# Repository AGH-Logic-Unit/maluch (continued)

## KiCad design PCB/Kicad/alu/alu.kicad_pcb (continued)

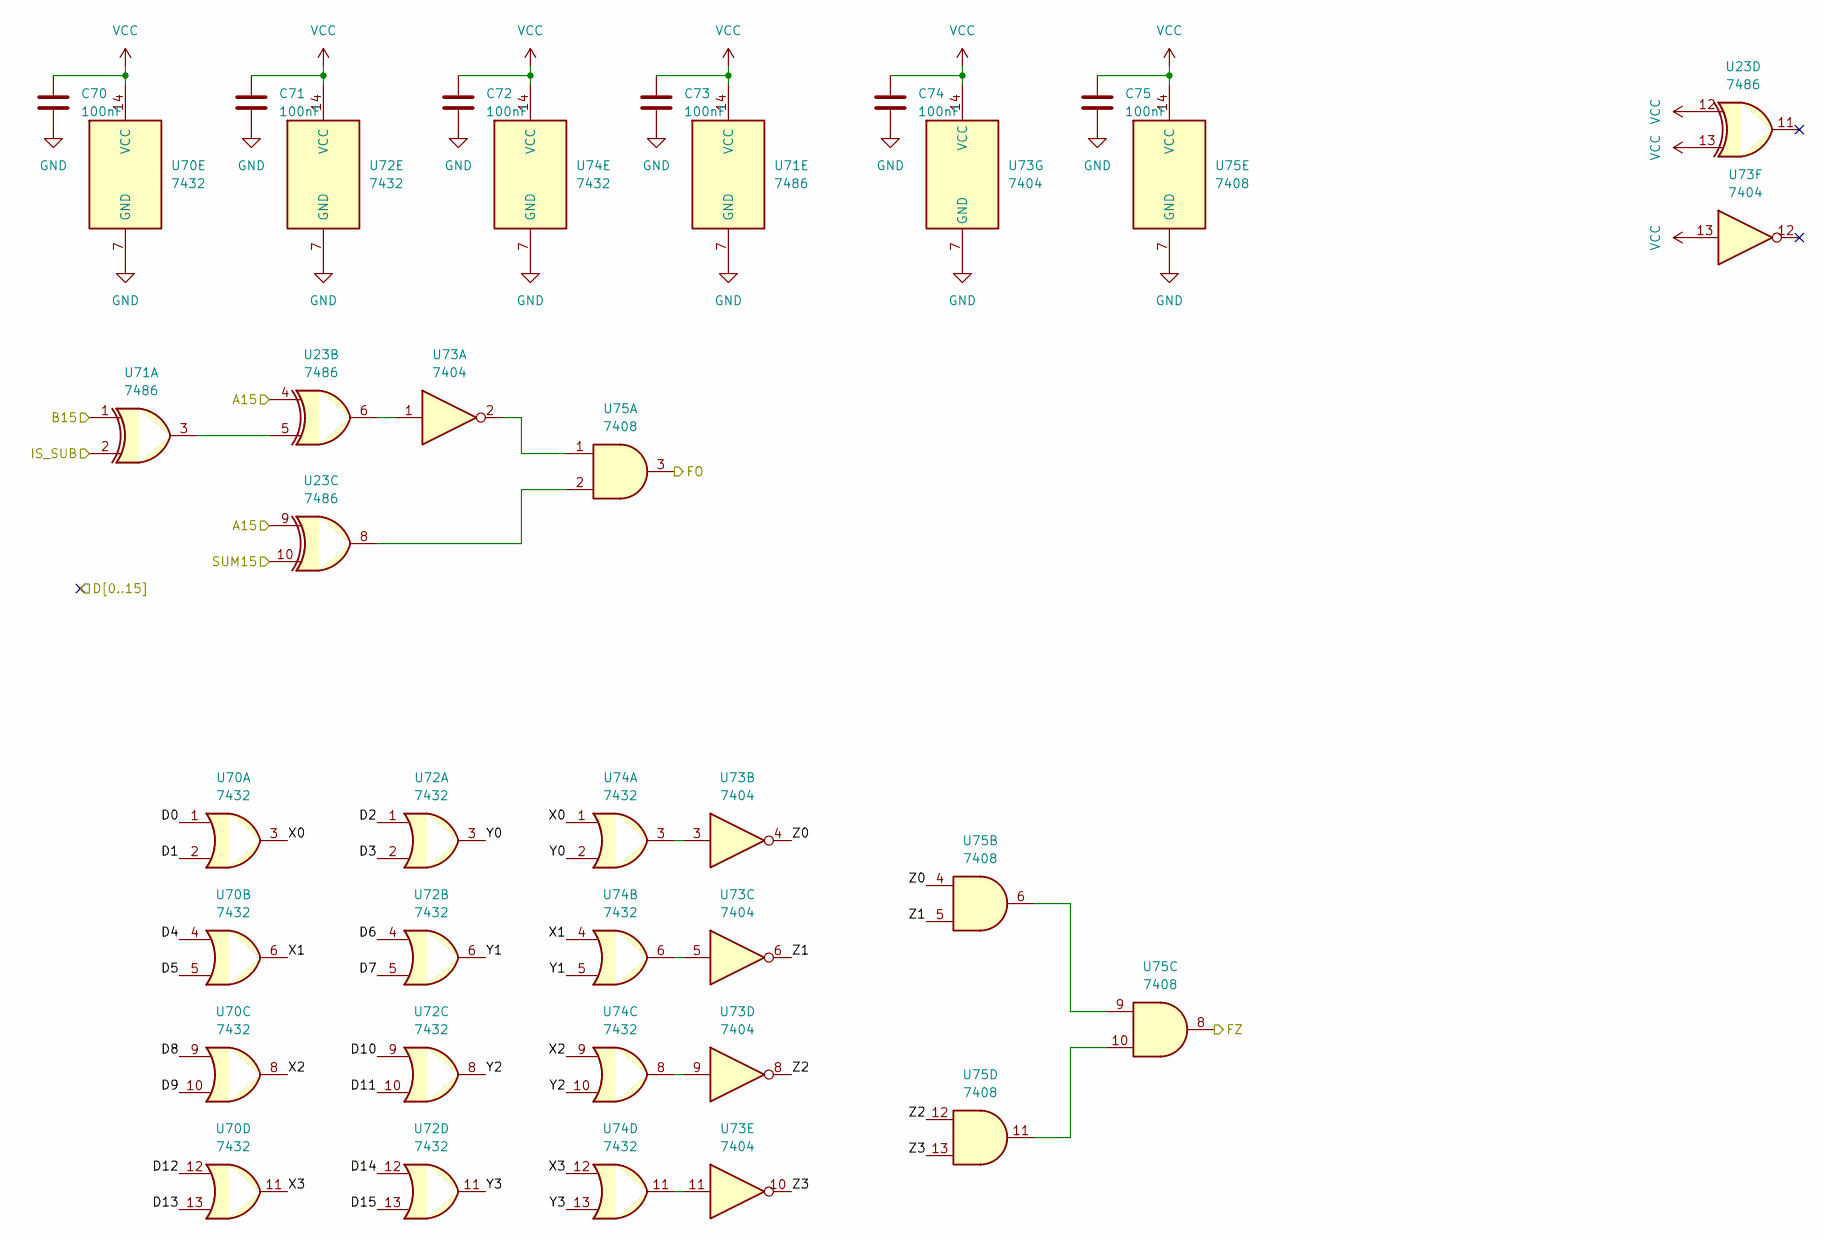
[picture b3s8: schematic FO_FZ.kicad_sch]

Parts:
C70, C71, C72, C73, C74, C75: 100nF; C_0402_1005Metric
U23, U71: 7486; SO-14_3.9x8.65mm_P1.27mm
U70, U72, U74: 7432; SO-14_3.9x8.65mm_P1.27mm
U73: 7404; SO-14_3.9x8.65mm_P1.27mm
U75: 7408; SO-14_3.9x8.65mm_P1.27mm

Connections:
/ADD_SUB15: U23.10; also elsewhere on the board
/A_BUS15: U23.4, U23.9; also elsewhere on the board
/B_BUS15: U71.1; also elsewhere on the board
/D0: U70.1; also elsewhere on the board
/D1: U70.2; also elsewhere on the board
/D2: U72.1; also elsewhere on the board
/D3: U72.2; also elsewhere on the board
/D4: U70.4; also elsewhere on the board
/D5: U70.5; also elsewhere on the board
/D6: U72.4; also elsewhere on the board
/D7: U72.5; also elsewhere on the board
/D8: U70.9; also elsewhere on the board
/D9: U70.10; also elsewhere on the board
/D10: U72.9; also elsewhere on the board
/D11: U72.10; also elsewhere on the board
/D12: U70.12; also elsewhere on the board
/D13: U70.13; also elsewhere on the board
/D14: U72.12; also elsewhere on the board
/D15: U72.13; also elsewhere on the board
/FO: U75.3; also elsewhere on the board
/FO_FZ/X0: U70.3, U74.1
/FO_FZ/X1: U70.6, U74.4
/FO_FZ/X2: U70.8, U74.9
/FO_FZ/X3: U70.11, U74.12
/FO_FZ/Y0: U72.3, U74.2
/FO_FZ/Y1: U72.6, U74.5
/FO_FZ/Y2: U72.8, U74.10
/FO_FZ/Y3: U72.11, U74.13
/FO_FZ/Z0: U73.4, U75.4
/FO_FZ/Z1: U73.6, U75.5
/FO_FZ/Z2: U73.8, U75.12
/FO_FZ/Z3: U73.10, U75.13
/FZ: U75.8; also elsewhere on the board
/IS_SUB: U71.2; also elsewhere on the board
GND: C70.2, C71.2, C72.2, C73.2, C74.2, C75.2, U70.7 (GND), U71.7 (GND), U72.7 (GND), U73.7 (GND), U74.7 (GND), U75.7 (GND); also elsewhere on the board
unnamed: U23.5, U71.3
unnamed: U23.6, U73.1
unnamed: U23.8, U75.2
unnamed: U73.2, U75.1
unnamed: U73.3, U74.3
unnamed: U73.5, U74.6
unnamed: U73.9, U74.8
unnamed: U73.11, U74.11
unnamed: U75.6, U75.9
unnamed: U75.10, U75.11
VCC: C70.1, C71.1, C72.1, C73.1, C74.1, C75.1, U23.12, U23.13, U70.14 (VCC), U71.14 (VCC), U72.14 (VCC), U73.13, U73.14 (VCC), U74.14 (VCC), U75.14 (VCC); also elsewhere on the board

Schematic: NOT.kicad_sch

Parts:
C14, C15, C16: 100nF; C_0402_1005Metric
U2, U15, U16: 7404; SO-14_3.9x8.65mm_P1.27mm

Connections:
/B_BUS0: U2.5; also elsewhere on the board
/B_BUS1: U2.9; also elsewhere on the board
/B_BUS2: U15.11; also elsewhere on the board
/B_BUS3: U15.13; also elsewhere on the board
/B_BUS4: U2.1; also elsewhere on the board
/B_BUS5: U2.3; also elsewhere on the board
/B_BUS6: U15.5; also elsewhere on the board
/B_BUS7: U15.9; also elsewhere on the board
/B_BUS8: U15.1; also elsewhere on the board
/B_BUS9: U15.3; also elsewhere on the board
/B_BUS10: U16.5; also elsewhere on the board
/B_BUS11: U16.9; also elsewhere on the board
/B_BUS12: U16.11; also elsewhere on the board
/B_BUS13: U16.13; also elsewhere on the board
/B_BUS14: U16.1; also elsewhere on the board
/B_BUS15: U16.3; also elsewhere on the board
/NOT0: U2.6; also elsewhere on the board
/NOT1: U2.8; also elsewhere on the board
/NOT2: U15.10; also elsewhere on the board
/NOT3: U15.12; also elsewhere on the board
/NOT4: U2.2; also elsewhere on the board
/NOT5: U2.4; also elsewhere on the board
/NOT6: U15.6; also elsewhere on the board
/NOT7: U15.8; also elsewhere on the board
/NOT8: U15.2; also elsewhere on the board
/NOT9: U15.4; also elsewhere on the board
/NOT10: U16.6; also elsewhere on the board
/NOT11: U16.8; also elsewhere on the board
/NOT12: U16.10; also elsewhere on the board
/NOT13: U16.12; also elsewhere on the board
/NOT14: U16.2; also elsewhere on the board
/NOT15: U16.4; also elsewhere on the board
GND: C14.2, C15.2, C16.2, U2.7 (GND), U15.7 (GND), U16.7 (GND); also elsewhere on the board
VCC: C14.1, C15.1, C16.1, U2.14 (VCC), U15.14 (VCC), U16.14 (VCC); also elsewhere on the board

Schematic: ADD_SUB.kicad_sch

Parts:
C17, C18, C19, C20, C21, C22, C23, C24, C25: 100nF; C_0402_1005Metric
U17, U18, U19, U22, U23: 7486; SO-14_3.9x8.65mm_P1.27mm
U20, U21, U24, U25: 74283; SOIC-16_3.9x9.9mm_P1.27mm

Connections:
/ADD_SUB0: U20.4 (S1); also elsewhere on the board
/ADD_SUB1: U20.1 (S2); also elsewhere on the board
/ADD_SUB2: U20.13 (S3); also elsewhere on the board
/ADD_SUB3: U20.10 (S4); also elsewhere on the board
/ADD_SUB4: U21.4 (S1); also elsewhere on the board
/ADD_SUB5: U21.1 (S2); also elsewhere on the board
/ADD_SUB6: U21.13 (S3); also elsewhere on the board
/ADD_SUB7: U21.10 (S4); also elsewhere on the board
/ADD_SUB8: U24.4 (S1); also elsewhere on the board
/ADD_SUB9: U24.1 (S2); also elsewhere on the board
/ADD_SUB10: U24.13 (S3); also elsewhere on the board
/ADD_SUB11: U24.10 (S4); also elsewhere on the board
/ADD_SUB12: U25.4 (S1); also elsewhere on the board
/ADD_SUB13: U25.1 (S2); also elsewhere on the board
/ADD_SUB14: U25.13 (S3); also elsewhere on the board
/ADD_SUB15: U25.10 (S4); also elsewhere on the board
/ADD_SUB/COUT0: U20.9 (C4), U21.7 (C0)
/ADD_SUB/COUT1: U21.9 (C4), U24.7 (C0)
/ADD_SUB/COUT2: U24.9 (C4), U25.7 (C0)
/A_BUS0: U20.12 (A4); also elsewhere on the board
/A_BUS1: U20.14 (A3); also elsewhere on the board
/A_BUS2: U20.3 (A2); also elsewhere on the board
/A_BUS3: U20.5 (A1); also elsewhere on the board
/A_BUS4: U21.12 (A4); also elsewhere on the board
/A_BUS5: U21.14 (A3); also elsewhere on the board
/A_BUS6: U21.3 (A2); also elsewhere on the board
/A_BUS7: U21.5 (A1); also elsewhere on the board
/A_BUS8: U24.12 (A4); also elsewhere on the board
/A_BUS9: U24.14 (A3); also elsewhere on the board
/A_BUS10: U24.3 (A2); also elsewhere on the board
/A_BUS11: U24.5 (A1); also elsewhere on the board
/A_BUS12: U25.12 (A4); also elsewhere on the board
/A_BUS13: U25.14 (A3); also elsewhere on the board
/A_BUS14: U25.3 (A2); also elsewhere on the board
/A_BUS15: U25.5 (A1); also elsewhere on the board
/B_BUS0: U18.2; also elsewhere on the board
/B_BUS1: U17.5; also elsewhere on the board
/B_BUS2: U17.10; also elsewhere on the board
/B_BUS3: U17.13; also elsewhere on the board
/B_BUS4: U19.2, U23.2; also elsewhere on the board
/B_BUS5: U18.5, U22.5; also elsewhere on the board
/B_BUS6: U18.10, U22.10; also elsewhere on the board
/B_BUS7: U18.13, U22.13; also elsewhere on the board
/B_BUS8: U22.2; also elsewhere on the board
/B_BUS9: U19.5; also elsewhere on the board
/B_BUS10: U19.10; also elsewhere on the board
/B_BUS11: U19.13; also elsewhere on the board
/FC: U25.9 (C4); also elsewhere on the board
/IS_SUB: U17.1, U17.4, U17.9, U17.12, U18.1, U18.4, U18.9, U18.12, U19.1, U19.4, U19.9, U19.12, U22.1, U22.4, U22.9, U22.12, U23.1; also elsewhere on the board
GND: C17.2, C18.2, C19.2, C20.2, C21.2, C22.2, C23.2, C24.2, C25.2, U17.2, U17.7 (GND), U18.7 (GND), U19.7 (GND), U20.8 (GND), U21.8 (GND), U22.7 (GND), U23.7 (GND), U24.8 (GND), U25.8 (GND); also elsewhere on the board
unnamed: U18.3, U20.6 (B1)
unnamed: U17.6, U20.2 (B2)
unnamed: U17.8, U20.15 (B3)
unnamed: U17.11, U20.11 (B4)
unnamed: U17.3, U20.7 (C0)
unnamed: U19.3, U21.6 (B1)
unnamed: U18.6, U21.2 (B2)
unnamed: U18.8, U21.15 (B3)
unnamed: U18.11, U21.11 (B4)
unnamed: U22.3, U24.6 (B1)
unnamed: U19.6, U24.2 (B2)
unnamed: U19.8, U24.15 (B3)
unnamed: U19.11, U24.11 (B4)
unnamed: U23.3, U25.6 (B1)
unnamed: U22.6, U25.2 (B2)
unnamed: U22.8, U25.15 (B3)
unnamed: U22.11, U25.11 (B4)
VCC: C17.1, C18.1, C19.1, C20.1, C21.1, C22.1, C23.1, C24.1, C25.1, U17.14 (VCC), U18.14 (VCC), U19.14 (VCC), U20.16 (VCC), U21.16 (VCC), U22.14 (VCC), U23.14 (VCC), U24.16 (VCC), U25.16 (VCC); also elsewhere on the board

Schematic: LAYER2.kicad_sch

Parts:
C34, C35, C36, C37: 100nF; C_0402_1005Metric
U34, U35, U36, U37: 74257; SOIC-16_3.9x9.9mm_P1.27mm

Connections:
/B_BUS1: U34.1 (S), U35.1 (S), U36.1 (S), U37.1 (S); also elsewhere on the board
/SHIFT_REG/LAYER1/Lout0: U34.2 (I0a); also elsewhere on the board
/SHIFT_REG/LAYER1/Lout1: U34.5 (I0b); also elsewhere on the board
/SHIFT_REG/LAYER1/Lout2: U34.3 (I1a), U34.14 (I0c); also elsewhere on the board
/SHIFT_REG/LAYER1/Lout3: U34.6 (I1b), U34.11 (I0d); also elsewhere on the board
/SHIFT_REG/LAYER1/Lout4: U34.13 (I1c), U35.2 (I0a); also elsewhere on the board
/SHIFT_REG/LAYER1/Lout5: U34.10 (I1d), U35.5 (I0b); also elsewhere on the board
/SHIFT_REG/LAYER1/Lout6: U35.3 (I1a), U35.14 (I0c); also elsewhere on the board
/SHIFT_REG/LAYER1/Lout7: U35.6 (I1b), U35.11 (I0d); also elsewhere on the board
/SHIFT_REG/LAYER1/Lout8: U35.13 (I1c), U36.2 (I0a); also elsewhere on the board
/SHIFT_REG/LAYER1/Lout9: U35.10 (I1d), U36.5 (I0b); also elsewhere on the board
/SHIFT_REG/LAYER1/Lout10: U36.3 (I1a), U36.14 (I0c); also elsewhere on the board
/SHIFT_REG/LAYER1/Lout11: U36.6 (I1b), U36.11 (I0d); also elsewhere on the board
/SHIFT_REG/LAYER1/Lout12: U36.13 (I1c), U37.2 (I0a); also elsewhere on the board
/SHIFT_REG/LAYER1/Lout13: U36.10 (I1d), U37.5 (I0b); also elsewhere on the board
/SHIFT_REG/LAYER1/Lout14: U37.3 (I1a), U37.14 (I0c); also elsewhere on the board
/SHIFT_REG/LAYER1/Lout15: U37.6 (I1b), U37.11 (I0d); also elsewhere on the board
/SHIFT_REG/LAYER2/Lout0: U34.4 (Za); also elsewhere on the board
/SHIFT_REG/LAYER2/Lout1: U34.7 (Zb); also elsewhere on the board
/SHIFT_REG/LAYER2/Lout2: U34.12 (Zc); also elsewhere on the board
/SHIFT_REG/LAYER2/Lout3: U34.9 (Zd); also elsewhere on the board
/SHIFT_REG/LAYER2/Lout4: U35.4 (Za); also elsewhere on the board
/SHIFT_REG/LAYER2/Lout5: U35.7 (Zb); also elsewhere on the board
/SHIFT_REG/LAYER2/Lout6: U35.12 (Zc); also elsewhere on the board
/SHIFT_REG/LAYER2/Lout7: U35.9 (Zd); also elsewhere on the board
/SHIFT_REG/LAYER2/Lout8: U36.4 (Za); also elsewhere on the board
/SHIFT_REG/LAYER2/Lout9: U36.7 (Zb); also elsewhere on the board
/SHIFT_REG/LAYER2/Lout10: U36.12 (Zc); also elsewhere on the board
/SHIFT_REG/LAYER2/Lout11: U36.9 (Zd); also elsewhere on the board
/SHIFT_REG/LAYER2/Lout12: U37.4 (Za); also elsewhere on the board
/SHIFT_REG/LAYER2/Lout13: U37.7 (Zb); also elsewhere on the board
/SHIFT_REG/LAYER2/Lout14: U37.12 (Zc); also elsewhere on the board
/SHIFT_REG/LAYER2/Lout15: U37.9 (Zd); also elsewhere on the board
GND: C34.2, C35.2, C36.2, C37.2, U34.8 (GND), U34.15 (OE), U35.8 (GND), U35.15 (OE), U36.8 (GND), U36.15 (OE), U37.8 (GND), U37.10 (I1d), U37.13 (I1c), U37.15 (OE); also elsewhere on the board
VCC: C34.1, C35.1, C36.1, C37.1, U34.16 (VCC), U35.16 (VCC), U36.16 (VCC), U37.16 (VCC); also elsewhere on the board

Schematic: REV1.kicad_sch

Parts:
C26, C27, C28, C29: 100nF; C_0402_1005Metric
U26, U27, U28, U29: 74257; SOIC-16_3.9x9.9mm_P1.27mm

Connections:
/A_BUS0: U26.2 (I0a), U29.10 (I1d); also elsewhere on the board
/A_BUS1: U26.5 (I0b), U29.13 (I1c); also elsewhere on the board
/A_BUS2: U26.14 (I0c), U29.6 (I1b); also elsewhere on the board
/A_BUS3: U26.11 (I0d), U29.3 (I1a); also elsewhere on the board
/A_BUS4: U27.2 (I0a), U28.10 (I1d); also elsewhere on the board
/A_BUS5: U27.5 (I0b), U28.13 (I1c); also elsewhere on the board
/A_BUS6: U27.14 (I0c), U28.6 (I1b); also elsewhere on the board
/A_BUS7: U27.11 (I0d), U28.3 (I1a); also elsewhere on the board
/A_BUS8: U27.10 (I1d), U28.2 (I0a); also elsewhere on the board
/A_BUS9: U27.13 (I1c), U28.5 (I0b); also elsewhere on the board
/A_BUS10: U27.6 (I1b), U28.14 (I0c); also elsewhere on the board
/A_BUS11: U27.3 (I1a), U28.11 (I0d); also elsewhere on the board
/A_BUS12: U26.10 (I1d), U29.2 (I0a); also elsewhere on the board
/A_BUS13: U26.13 (I1c), U29.5 (I0b); also elsewhere on the board
/A_BUS14: U26.6 (I1b), U29.14 (I0c); also elsewhere on the board
/A_BUS15: U26.3 (I1a), U29.11 (I0d); also elsewhere on the board
/SHIFT_REG/LAYER1/R0: U26.4 (Za); also elsewhere on the board
/SHIFT_REG/LAYER1/R1: U26.7 (Zb); also elsewhere on the board
/SHIFT_REG/LAYER1/R2: U26.12 (Zc); also elsewhere on the board
/SHIFT_REG/LAYER1/R3: U26.9 (Zd); also elsewhere on the board
/SHIFT_REG/LAYER1/R4: U27.4 (Za); also elsewhere on the board
/SHIFT_REG/LAYER1/R5: U27.7 (Zb); also elsewhere on the board
/SHIFT_REG/LAYER1/R6: U27.12 (Zc); also elsewhere on the board
/SHIFT_REG/LAYER1/R7: U27.9 (Zd); also elsewhere on the board
/SHIFT_REG/LAYER1/R8: U28.4 (Za); also elsewhere on the board
/SHIFT_REG/LAYER1/R9: U28.7 (Zb); also elsewhere on the board
/SHIFT_REG/LAYER1/R10: U28.12 (Zc); also elsewhere on the board
/SHIFT_REG/LAYER1/R11: U28.9 (Zd); also elsewhere on the board
/SHIFT_REG/LAYER1/R12: U29.4 (Za); also elsewhere on the board
/SHIFT_REG/LAYER1/R13: U29.7 (Zb); also elsewhere on the board
/SHIFT_REG/LAYER1/R14: U29.12 (Zc); also elsewhere on the board
/SHIFT_REG/LAYER1/R15: U29.9 (Zd); also elsewhere on the board
/SHIFT_REG/REV: U26.1 (S), U27.1 (S), U28.1 (S), U29.1 (S); also elsewhere on the board
GND: C26.2, C27.2, C28.2, C29.2, U26.8 (GND), U26.15 (OE), U27.8 (GND), U27.15 (OE), U28.8 (GND), U28.15 (OE), U29.8 (GND), U29.15 (OE); also elsewhere on the board
VCC: C26.1, C27.1, C28.1, C29.1, U26.16 (VCC), U27.16 (VCC), U28.16 (VCC), U29.16 (VCC); also elsewhere on the board

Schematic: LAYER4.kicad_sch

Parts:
C42, C43, C44, C45: 100nF; C_0402_1005Metric
U42, U43, U44, U45: 74257; SOIC-16_3.9x9.9mm_P1.27mm

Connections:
/B_BUS3: U42.1 (S), U43.1 (S), U44.1 (S), U45.1 (S); also elsewhere on the board
/SHIFT_REG/LAYER3/Lout0: U42.2 (I0a); also elsewhere on the board
/SHIFT_REG/LAYER3/Lout1: U42.5 (I0b); also elsewhere on the board
/SHIFT_REG/LAYER3/Lout2: U42.14 (I0c); also elsewhere on the board
/SHIFT_REG/LAYER3/Lout3: U42.11 (I0d); also elsewhere on the board
/SHIFT_REG/LAYER3/Lout4: U43.2 (I0a); also elsewhere on the board
/SHIFT_REG/LAYER3/Lout5: U43.5 (I0b); also elsewhere on the board
/SHIFT_REG/LAYER3/Lout6: U43.14 (I0c); also elsewhere on the board
/SHIFT_REG/LAYER3/Lout7: U43.11 (I0d); also elsewhere on the board
/SHIFT_REG/LAYER3/Lout8: U42.3 (I1a), U44.2 (I0a); also elsewhere on the board
/SHIFT_REG/LAYER3/Lout9: U42.6 (I1b), U44.5 (I0b); also elsewhere on the board
/SHIFT_REG/LAYER3/Lout10: U42.13 (I1c), U44.14 (I0c); also elsewhere on the board
/SHIFT_REG/LAYER3/Lout11: U42.10 (I1d), U44.11 (I0d); also elsewhere on the board
/SHIFT_REG/LAYER3/Lout12: U43.3 (I1a), U45.2 (I0a); also elsewhere on the board
/SHIFT_REG/LAYER3/Lout13: U43.6 (I1b), U45.5 (I0b); also elsewhere on the board
/SHIFT_REG/LAYER3/Lout14: U43.13 (I1c), U45.14 (I0c); also elsewhere on the board
/SHIFT_REG/LAYER3/Lout15: U43.10 (I1d), U45.11 (I0d); also elsewhere on the board
/SHIFT_REG/LAYER4/Lout0: U42.4 (Za); also elsewhere on the board
/SHIFT_REG/LAYER4/Lout1: U42.7 (Zb); also elsewhere on the board
/SHIFT_REG/LAYER4/Lout2: U42.12 (Zc); also elsewhere on the board
/SHIFT_REG/LAYER4/Lout3: U42.9 (Zd); also elsewhere on the board
/SHIFT_REG/LAYER4/Lout4: U43.4 (Za); also elsewhere on the board
/SHIFT_REG/LAYER4/Lout5: U43.7 (Zb); also elsewhere on the board
/SHIFT_REG/LAYER4/Lout6: U43.12 (Zc); also elsewhere on the board
/SHIFT_REG/LAYER4/Lout7: U43.9 (Zd); also elsewhere on the board
/SHIFT_REG/LAYER4/Lout8: U44.4 (Za); also elsewhere on the board
/SHIFT_REG/LAYER4/Lout9: U44.7 (Zb); also elsewhere on the board
/SHIFT_REG/LAYER4/Lout10: U44.12 (Zc); also elsewhere on the board
/SHIFT_REG/LAYER4/Lout11: U44.9 (Zd); also elsewhere on the board
/SHIFT_REG/LAYER4/Lout12: U45.4 (Za); also elsewhere on the board
/SHIFT_REG/LAYER4/Lout13: U45.7 (Zb); also elsewhere on the board
/SHIFT_REG/LAYER4/Lout14: U45.12 (Zc); also elsewhere on the board
/SHIFT_REG/LAYER4/Lout15: U45.9 (Zd); also elsewhere on the board
GND: C42.2, C43.2, C44.2, C45.2, U42.8 (GND), U42.15 (OE), U43.8 (GND), U43.15 (OE), U44.3 (I1a), U44.6 (I1b), U44.8 (GND), U44.10 (I1d), U44.13 (I1c), U44.15 (OE), U45.3 (I1a), U45.6 (I1b), U45.8 (GND), U45.10 (I1d), U45.13 (I1c), U45.15 (OE); also elsewhere on the board
VCC: C42.1, C43.1, C44.1, C45.1, U42.16 (VCC), U43.16 (VCC), U44.16 (VCC), U45.16 (VCC); also elsewhere on the board

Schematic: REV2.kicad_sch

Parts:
C46, C47, C48, C49: 100nF; C_0402_1005Metric
U46, U47, U48, U49: 74257; SOIC-16_3.9x9.9mm_P1.27mm

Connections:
/SHIFT0: U46.4 (Za); also elsewhere on the board
/SHIFT1: U46.7 (Zb); also elsewhere on the board
/SHIFT2: U46.12 (Zc); also elsewhere on the board
/SHIFT3: U46.9 (Zd); also elsewhere on the board
/SHIFT4: U47.4 (Za); also elsewhere on the board
/SHIFT5: U47.7 (Zb); also elsewhere on the board
/SHIFT6: U47.12 (Zc); also elsewhere on the board
/SHIFT7: U47.9 (Zd); also elsewhere on the board
/SHIFT8: U48.4 (Za); also elsewhere on the board
/SHIFT9: U48.7 (Zb); also elsewhere on the board
/SHIFT10: U48.12 (Zc); also elsewhere on the board
/SHIFT11: U48.9 (Zd); also elsewhere on the board
/SHIFT12: U49.4 (Za); also elsewhere on the board
/SHIFT13: U49.7 (Zb); also elsewhere on the board
/SHIFT14: U49.12 (Zc); also elsewhere on the board
/SHIFT15: U49.9 (Zd); also elsewhere on the board
/SHIFT_REG/LAYER4/Lout0: U46.2 (I0a), U49.10 (I1d); also elsewhere on the board
/SHIFT_REG/LAYER4/Lout1: U46.5 (I0b), U49.13 (I1c); also elsewhere on the board
/SHIFT_REG/LAYER4/Lout2: U46.14 (I0c), U49.6 (I1b); also elsewhere on the board
/SHIFT_REG/LAYER4/Lout3: U46.11 (I0d), U49.3 (I1a); also elsewhere on the board
/SHIFT_REG/LAYER4/Lout4: U47.2 (I0a), U48.10 (I1d); also elsewhere on the board
/SHIFT_REG/LAYER4/Lout5: U47.5 (I0b), U48.13 (I1c); also elsewhere on the board
/SHIFT_REG/LAYER4/Lout6: U47.14 (I0c), U48.6 (I1b); also elsewhere on the board
/SHIFT_REG/LAYER4/Lout7: U47.11 (I0d), U48.3 (I1a); also elsewhere on the board
/SHIFT_REG/LAYER4/Lout8: U47.10 (I1d), U48.2 (I0a); also elsewhere on the board
/SHIFT_REG/LAYER4/Lout9: U47.13 (I1c), U48.5 (I0b); also elsewhere on the board
/SHIFT_REG/LAYER4/Lout10: U47.6 (I1b), U48.14 (I0c); also elsewhere on the board
/SHIFT_REG/LAYER4/Lout11: U47.3 (I1a), U48.11 (I0d); also elsewhere on the board
/SHIFT_REG/LAYER4/Lout12: U46.10 (I1d), U49.2 (I0a); also elsewhere on the board
/SHIFT_REG/LAYER4/Lout13: U46.13 (I1c), U49.5 (I0b); also elsewhere on the board
/SHIFT_REG/LAYER4/Lout14: U46.6 (I1b), U49.14 (I0c); also elsewhere on the board
/SHIFT_REG/LAYER4/Lout15: U46.3 (I1a), U49.11 (I0d); also elsewhere on the board
/SHIFT_REG/REV: U46.1 (S), U47.1 (S), U48.1 (S), U49.1 (S); also elsewhere on the board
GND: C46.2, C47.2, C48.2, C49.2, U46.8 (GND), U46.15 (OE), U47.8 (GND), U47.15 (OE), U48.8 (GND), U48.15 (OE), U49.8 (GND), U49.15 (OE); also elsewhere on the board
VCC: C46.1, C47.1, C48.1, C49.1, U46.16 (VCC), U47.16 (VCC), U48.16 (VCC), U49.16 (VCC); also elsewhere on the board

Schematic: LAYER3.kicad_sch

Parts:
C38, C39, C40, C41: 100nF; C_0402_1005Metric
U38, U39, U40, U41: 74257; SOIC-16_3.9x9.9mm_P1.27mm

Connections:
/B_BUS2: U38.1 (S), U39.1 (S), U40.1 (S), U41.1 (S); also elsewhere on the board
/SHIFT_REG/LAYER2/Lout0: U38.2 (I0a); also elsewhere on the board
/SHIFT_REG/LAYER2/Lout1: U38.5 (I0b); also elsewhere on the board
/SHIFT_REG/LAYER2/Lout2: U38.14 (I0c); also elsewhere on the board
/SHIFT_REG/LAYER2/Lout3: U38.11 (I0d); also elsewhere on the board
/SHIFT_REG/LAYER2/Lout4: U38.3 (I1a), U39.2 (I0a); also elsewhere on the board
/SHIFT_REG/LAYER2/Lout5: U38.6 (I1b), U39.5 (I0b); also elsewhere on the board
/SHIFT_REG/LAYER2/Lout6: U38.13 (I1c), U39.14 (I0c); also elsewhere on the board
/SHIFT_REG/LAYER2/Lout7: U38.10 (I1d), U39.11 (I0d); also elsewhere on the board
/SHIFT_REG/LAYER2/Lout8: U39.3 (I1a), U40.2 (I0a); also elsewhere on the board
/SHIFT_REG/LAYER2/Lout9: U39.6 (I1b), U40.5 (I0b); also elsewhere on the board
/SHIFT_REG/LAYER2/Lout10: U39.13 (I1c), U40.14 (I0c); also elsewhere on the board
/SHIFT_REG/LAYER2/Lout11: U39.10 (I1d), U40.11 (I0d); also elsewhere on the board
/SHIFT_REG/LAYER2/Lout12: U40.3 (I1a), U41.2 (I0a); also elsewhere on the board
/SHIFT_REG/LAYER2/Lout13: U40.6 (I1b), U41.5 (I0b); also elsewhere on the board
/SHIFT_REG/LAYER2/Lout14: U40.13 (I1c), U41.14 (I0c); also elsewhere on the board
/SHIFT_REG/LAYER2/Lout15: U40.10 (I1d), U41.11 (I0d); also elsewhere on the board
/SHIFT_REG/LAYER3/Lout0: U38.4 (Za); also elsewhere on the board
/SHIFT_REG/LAYER3/Lout1: U38.7 (Zb); also elsewhere on the board
/SHIFT_REG/LAYER3/Lout2: U38.12 (Zc); also elsewhere on the board
/SHIFT_REG/LAYER3/Lout3: U38.9 (Zd); also elsewhere on the board
/SHIFT_REG/LAYER3/Lout4: U39.4 (Za); also elsewhere on the board
/SHIFT_REG/LAYER3/Lout5: U39.7 (Zb); also elsewhere on the board
/SHIFT_REG/LAYER3/Lout6: U39.12 (Zc); also elsewhere on the board
/SHIFT_REG/LAYER3/Lout7: U39.9 (Zd); also elsewhere on the board
/SHIFT_REG/LAYER3/Lout8: U40.4 (Za); also elsewhere on the board
/SHIFT_REG/LAYER3/Lout9: U40.7 (Zb); also elsewhere on the board
/SHIFT_REG/LAYER3/Lout10: U40.12 (Zc); also elsewhere on the board
/SHIFT_REG/LAYER3/Lout11: U40.9 (Zd); also elsewhere on the board
/SHIFT_REG/LAYER3/Lout12: U41.4 (Za); also elsewhere on the board
/SHIFT_REG/LAYER3/Lout13: U41.7 (Zb); also elsewhere on the board
/SHIFT_REG/LAYER3/Lout14: U41.12 (Zc); also elsewhere on the board
/SHIFT_REG/LAYER3/Lout15: U41.9 (Zd); also elsewhere on the board
GND: C38.2, C39.2, C40.2, C41.2, U38.8 (GND), U38.15 (OE), U39.8 (GND), U39.15 (OE), U40.8 (GND), U40.15 (OE), U41.3 (I1a), U41.6 (I1b), U41.8 (GND), U41.10 (I1d), U41.13 (I1c), U41.15 (OE); also elsewhere on the board
VCC: C38.1, C39.1, C40.1, C41.1, U38.16 (VCC), U39.16 (VCC), U40.16 (VCC), U41.16 (VCC); also elsewhere on the board

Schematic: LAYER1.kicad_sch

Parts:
C30, C31, C32, C33: 100nF; C_0402_1005Metric
U30, U31, U32, U33: 74257; SOIC-16_3.9x9.9mm_P1.27mm

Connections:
/B_BUS0: U30.1 (S), U31.1 (S), U32.1 (S), U33.1 (S); also elsewhere on the board
/SHIFT_REG/LAYER1/Lout0: U30.4 (Za); also elsewhere on the board
/SHIFT_REG/LAYER1/Lout1: U30.7 (Zb); also elsewhere on the board
/SHIFT_REG/LAYER1/Lout2: U30.12 (Zc); also elsewhere on the board
/SHIFT_REG/LAYER1/Lout3: U30.9 (Zd); also elsewhere on the board
/SHIFT_REG/LAYER1/Lout4: U31.4 (Za); also elsewhere on the board
/SHIFT_REG/LAYER1/Lout5: U31.7 (Zb); also elsewhere on the board
/SHIFT_REG/LAYER1/Lout6: U31.12 (Zc); also elsewhere on the board
/SHIFT_REG/LAYER1/Lout7: U31.9 (Zd); also elsewhere on the board
/SHIFT_REG/LAYER1/Lout8: U32.4 (Za); also elsewhere on the board
/SHIFT_REG/LAYER1/Lout9: U32.7 (Zb); also elsewhere on the board
/SHIFT_REG/LAYER1/Lout10: U32.12 (Zc); also elsewhere on the board
/SHIFT_REG/LAYER1/Lout11: U32.9 (Zd); also elsewhere on the board
/SHIFT_REG/LAYER1/Lout12: U33.4 (Za); also elsewhere on the board
/SHIFT_REG/LAYER1/Lout13: U33.7 (Zb); also elsewhere on the board
/SHIFT_REG/LAYER1/Lout14: U33.12 (Zc); also elsewhere on the board
/SHIFT_REG/LAYER1/Lout15: U33.9 (Zd); also elsewhere on the board
/SHIFT_REG/LAYER1/R0: U30.2 (I0a); also elsewhere on the board
/SHIFT_REG/LAYER1/R1: U30.3 (I1a), U30.5 (I0b); also elsewhere on the board
/SHIFT_REG/LAYER1/R2: U30.6 (I1b), U30.14 (I0c); also elsewhere on the board
/SHIFT_REG/LAYER1/R3: U30.11 (I0d), U30.13 (I1c); also elsewhere on the board
/SHIFT_REG/LAYER1/R4: U30.10 (I1d), U31.2 (I0a); also elsewhere on the board
/SHIFT_REG/LAYER1/R5: U31.3 (I1a), U31.5 (I0b); also elsewhere on the board
/SHIFT_REG/LAYER1/R6: U31.6 (I1b), U31.14 (I0c); also elsewhere on the board
/SHIFT_REG/LAYER1/R7: U31.11 (I0d), U31.13 (I1c); also elsewhere on the board
/SHIFT_REG/LAYER1/R8: U31.10 (I1d), U32.2 (I0a); also elsewhere on the board
/SHIFT_REG/LAYER1/R9: U32.3 (I1a), U32.5 (I0b); also elsewhere on the board
/SHIFT_REG/LAYER1/R10: U32.6 (I1b), U32.14 (I0c); also elsewhere on the board
/SHIFT_REG/LAYER1/R11: U32.11 (I0d), U32.13 (I1c); also elsewhere on the board
/SHIFT_REG/LAYER1/R12: U32.10 (I1d), U33.2 (I0a); also elsewhere on the board
/SHIFT_REG/LAYER1/R13: U33.3 (I1a), U33.5 (I0b); also elsewhere on the board
/SHIFT_REG/LAYER1/R14: U33.6 (I1b), U33.14 (I0c); also elsewhere on the board
/SHIFT_REG/LAYER1/R15: U33.11 (I0d), U33.13 (I1c); also elsewhere on the board
GND: C30.2, C31.2, C32.2, C33.2, U30.8 (GND), U30.15 (OE), U31.8 (GND), U31.15 (OE), U32.8 (GND), U32.15 (OE), U33.8 (GND), U33.10 (I1d), U33.15 (OE); also elsewhere on the board
VCC: C30.1, C31.1, C32.1, C33.1, U30.16 (VCC), U31.16 (VCC), U32.16 (VCC), U33.16 (VCC); also elsewhere on the board

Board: 6 copper layers, 230 parts (0 on the bottom side), 335 nets, no tracks yet.

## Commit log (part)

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2025-10-25 fix: ascii_address calculation change, display color
2025-10-26 finished control unit ; added ROMs
2025-10-27 add pinheader to pcb lib
2025-10-27 alu schematic and board wip
2025-10-31 memory controller 74xx
2025-11-03 Added debouncer
2025-11-04 Added clear_engine
2025-11-10 memory controller 74
2025-11-16 template update
2025-11-16 wrong file used previously ; fixed name
2025-11-19 refactor for working branching
2025-11-19 basic core working
2025-11-19 migrate core interface to core_i
2025-11-19 add preprocesor optimization for importing modules
2025-11-19 create precision simulation and add basic test for counter
2025-11-19 Optimize top testbench
2025-11-19 Change mem bus to 32b
2025-11-19 Memory core functionality
2025-11-19 Added working graphics card
2025-11-19 Added working graphics card module
2025-11-19 Added vga_controller.sv file
2025-11-19 Minor fixed, mainly directory path strings
2025-11-19 Added graphics_card testbench and char_rom memory
2025-11-19 Code changes
2025-11-19 Revert "Code changes"
    This reverts commit a699a3ead8c12b348adec7c25efd6674342bfa04.
2025-11-19 Deleted single pixel coloring
2025-11-19 Added trial2png file for testbenching and corrected gpu data output
2025-11-19 Changed vram_address length
2025-11-19 Code cleanup
2025-11-22 io control version on 74xx
2025-11-22 update specification of GPU
2025-11-22 Io docs (#16)
    * IO documentation
2025-11-22 74xx implementation of register file
2025-11-23 74xx implementation of register file (#17)
2025-11-25 kicad mem controller
2025-12-06 memory controler fix
2025-12-07 Added ps2 keyboard controller tb
2025-12-07 Changed name of the file to the proper one
2025-12-07 Refactoring ps2 keyboard controller
2025-12-07 initial testing of external IP
2025-12-11 kicad fix
2025-12-13 kicad memory controler
2025-12-23 Added io_w_en signal and separation of combinational logic of outputs
2025-12-23 Updated testbench
2025-12-23 memory controler kicad (#20)
    * kicad mem controller
    * fix
    * memory controler fix
    * memory controler fix
    * kicad fix
    * kicad memory controler
2025-12-23 Fixed nameing in ps2_keyboard_controller
2025-12-27 first draft of io controller sch
2025-12-30 initial version of io controller schematic
2026-01-04 Route D[0..15] data bus and control signals to J2 and J3
2026-01-04 Add Flags_Logic module with 74LS175 register and 74HC688-based zero detection
2026-01-11 Add support for IN and OUT instructions to the decoder
2026-01-11 Add decoder IN/OUT instructions testbench
2026-01-12 Reformat ports in decoder
2026-01-12 Add memory controller driver, with LDW/STW instruction support
2026-01-12 Add failed tests counter to decoder_tb
2026-01-12 Add LDW/STW instruction tests to decoder_tb
2026-01-16 forgot makefile ; fixed simulator bug
2026-01-16 changed interrupt mechanism
2026-01-16 bugfix
2026-01-16 bugfix: source
2026-01-16 removed hlt
2026-01-16 isa update
2026-01-16 QoL stuff ; show command
2026-01-17 Move outcome_driver logic into register_driver
2026-01-19 Refactore decoder
2026-01-19 One reset at beginning, and IN condition fix
2026-01-19 Add signal to control csr
2026-01-19 Rename decoder to control_unit
2026-01-19 Add stack pointer and register_file testbench
2026-01-19 Add support for PUSH instruction
2026-01-19 Add PUSH instruction test to control_unit_tb
2026-01-20 Modified register_file to support paraller writing to Rd and SP
2026-01-20 Add support for PULL instruction
2026-01-20 Add PULL instruction test to control_unit_tb
2026-01-20 Add REG_SP parameter
2026-01-20 Change _reset to active-low in register_file
2026-02-08 Adapt counter to updated design assumptions
2026-02-08 Code cleanup and refactore
2026-02-08 Port counter testbench to Verilator C++
2026-02-08 Rename module to program_counter
2026-02-08 Add support for branch instructions
2026-02-08 Add branch instructions test to control_unit_tb
2026-02-09 Fix some drivers not handling immediate
2026-02-09 Fix wrong reset polarity in register_file
2026-02-09 Change std::vector to std::array in progmem
2026-02-09 Add support for CALL instruction in control_unit
2026-02-09 Add CALL instruction test to control_unit_tb
2026-02-09 Add support for CALL instruction in program_counter
2026-02-09 Add CALL instruction test to program_counter_tb
2026-02-09 Update module interconnections in core
2026-02-09 Add function to handle insctructions read
2026-02-09 Adapt core_tb to updated design assumptions
2026-02-09 Fix in program_counter, not handling immediate
2026-02-09 Fix program_counter_tb, wrong immediate testing
2026-02-09 Add instruction encoder in program_counter_tb
2026-02-09 Code refactore in program_counter_tb
2026-02-09 Update instruction encoder in control_unit_tb
2026-02-09 PUSH instruction code refactore
2026-02-09 Update instruction tests, now testing immediate too
2026-02-09 Add support for RET instruction in control_unit
2026-02-09 Add RET instruction test to control_unit_tb
2026-02-09 Code cleanup in control_unit_tb
2026-02-09 Add support for RET instruction in program_counter
2026-02-09 Add RET instruction test to program_counter_tb
2026-02-09 Fix CALL/RET instruction test condition in program_counter_tb
2026-02-09 Add support for MOV instruction
2026-02-09 Add MOV instruction test to control_unit_tb
2026-02-09 Add support for CMP/TEST instructions with reserved functs
2026-02-09 Add CMP/TEST/reserved instructions test to control_unit_tb
2026-02-09 Fix fatal flaw - wrongly handled OUT/STW/PUSH in control_unit
2026-02-09 Fix fatal flaw - partialy checking register driver in some tests in control_unit_tb
2026-02-10 Add functions to handle data read/write
2026-02-10 Code refactore and memory handling in core_tb
2026-02-10 Example code to test some basic instructions
2026-02-10 Fix invalid opcode affecting instruction pointer
2026-02-10 Update core_tb to simulate instruction fetch delay and memory write delay
2026-02-10 Update example code to test more instructions
2026-02-10 Code refactore in control_unit
2026-02-10 control unit wip
2026-02-10 fix typo in timer docs
2026-02-13 Adapt ports nameing in core, and update them in core_tb
2026-02-16 few spice models
2026-02-16 io controller WIP ; simulated timer ; adjusted decoder ; adjusted LEDs
2026-02-21 Add GPU/VGA modules and tests
2026-02-23 more spice models and bugfixes ; more tests of io_controller - mostly keyboard
2026-02-24 primarily keyboard decoder finish ; preliminary layout
2026-02-25 fix documentation
2026-02-25 swap argument order in `in` opcode
    now it follows the dst, src convention
2026-02-25 add gpu types
2026-03-03 added a rudimentary disassembler
2026-03-03 Fix mistake that blocked simulation build
2026-03-03 Add IN/OUT basic handling in core_tb
2026-03-03 Update test program for core_tb
2026-03-07 pcb init
2026-03-09 Added memory controller
2026-03-09 Adapted memory
2026-03-11 name fix
2026-03-12 Add interrupt_controller
2026-03-12 Add interrupt_controller_tb
2026-03-12 Adapt core module and submodules, to support interrupts
2026-03-12 Update core_tb to support basic interrupt testing
2026-03-12 Fix wrong clock pulse width and tfp flush bug in core_tb
2026-03-12 Update core_tb program to test interrupts
2026-03-12 names
2026-03-12 memory controller
2026-03-12 alu behavioral model
2026-03-12 create kicad project template
2026-03-12 implementation of most features, lacks interrupts
2026-03-12 support for new int mechanism
2026-03-12 updated design document
2026-03-12 init
2026-03-12 unless bugs are found, finished interrupt design
2026-03-12 create lib for pcbs
2026-03-12 completed behavioral implementation
2026-03-12 implemented control unit using mostly 74xx chips
2026-03-12 GPU behavioral with VGA sync
2026-03-12 add pcb constraints
2026-03-12 interrupt bug fix
2026-03-12 bugfixes ; stylistic changes
2026-03-12 Revert "Merge branch 'pcb' of https://github.com/sarvl/maluch into pcb"
    This reverts commit 8762465c96191b8baaf434daf7fd6a710192f053, reversing
    changes made to c228ab879154aae27a8ab371f1c6d3d83fea3cab.
2026-03-12 fixing VGA sync order
2026-03-12 Reapply "Merge branch 'pcb' of https://github.com/sarvl/maluch into pcb"
    This reverts commit 931a64993b22d8fa83f97669744d0938aaa1e416.
2026-03-12 removed unnecessary connections
2026-03-12 74xx WIP
2026-03-12 started 74xx implementation; added ALU
2026-03-12 port name unification
2026-03-12 GPU without VGA sync
2026-03-13 control unit schematic
2026-03-14 work bus
2026-03-15 make simulator read binary files
2026-03-15 remove old assembler stuff
2026-03-18 change the assembly test tooling to use the new assembler
2026-03-18 removed unused `file.cpp` and `file.h`
2026-03-19 Author update
2026-03-22 LEDs + minor fixes
2026-03-22 Changed to Harvard architecture, TODO change data to 16b
2026-03-22 Memory tb done, TODO change after memory update
2026-03-22 Memory controller done, TODO change data to 16b
2026-03-22 Memory controller tb done TODO adjust after mem_ctr changes
2026-03-23 Memory_controller + Memory almost done. Backup if fail later
2026-03-23 Memory controller + Memory Done. Data path updated
2026-03-23 Finish memory controller
2026-03-23 Small Hotfix. Memory + Controller Done
2026-03-26 small bus changes
2026-03-29 samll fix and new problems
2026-03-30 LEDs added
    REGISTER.kicad_sch LEDs added to both REG_A and REG_B
2026-03-30 change_bus
2026-03-30 finish
2026-03-31 Footprints, PCB update
    Added footprints to all components, updated the PCB with the schematic
2026-03-31 everything_works
2026-03-31 capacitor
2026-04-02 Update PCB
2026-04-03 Enable inout support
2026-04-03 Driving kclk inout
2026-04-03 Delate PROCESSING state to omit problem with frames reception; Make some code refactor
2026-04-03 Add support for kclk inout
2026-04-03 Update ports name to match documentation
2026-04-03 memory controller schematic update
2026-04-03 fix disassembler
2026-04-03 Ported os_test.cpp to the new assembler
2026-04-04 ALU Pcb update
2026-04-04 Add io_bridge module
2026-04-04 Add io_bridge_tb
2026-04-04 Adapt ps2_keyboard_controller_tb
2026-04-08 Timer io pins renamed, added busy flag
2026-04-08 Added sim_precise.sh
2026-04-08 IO changes
2026-04-08 io controller update
2026-04-08 Forgot to add few things
2026-04-11 alu board adjustement
2026-04-11 control unit update
2026-04-13 Fix programmer FSM logic
2026-04-14 buscntrl placed
2026-04-14 Added crc module
2026-04-14 Added waveform output
2026-04-19 aaaaaaaaaaaaaaaaaaaaaaaaaaaaaaaaaaaaaaaaaaaa
2026-04-19 gggggggggggggggggggggggg
2026-04-20 Logisim 74xx implementation
2026-04-20 Kicad implementation
2026-04-20 gitignore
2026-04-20 bombardino crocodilo
2026-04-23 unify schematic
2026-04-24 too many LEDs
2026-04-27 check
2026-04-27 delete_led
2026-04-27 layout_1
2026-04-30 changes_1
2026-04-30 changes_2
2026-04-30 changes_3
2026-05-05 Stuff and layout
2026-05-09 every ic on layout
2026-05-10 implemented all monadic (unary) functions
2026-05-10 Ported all mnemonic macros to CALM instructions
2026-05-10 implemented all the dyadic (binary) opcodes
2026-05-10 swapped stw arguments (its correct now)
2026-05-10 Added mov instruction
2026-05-10 ported all the examples to assembly
2026-05-10 moved `test` out of the dyadic loop as it doesnt modify anything
2026-05-10 Added string support for db
2026-05-10 Added proper labels
2026-05-10 rename board to timer
2026-05-10 ported g00t00 and g00t01 to the new assembler
2026-05-10 overwritten `db` and `dw` directives
2026-05-10 implemented all the niladic (nullary) opcodes
2026-05-10 added fasmg proof of concept
2026-05-10 Add compontents for power
2026-05-15 remove backups
2026-05-17 CU routing mostly done, a bunch of control signals left
